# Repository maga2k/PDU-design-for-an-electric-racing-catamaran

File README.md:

# PDU-design-for-an-electric-racing-catamaran
Hardware and firmware implementation of a Power Distribution Unit (PDU) for an electric racing catamaran

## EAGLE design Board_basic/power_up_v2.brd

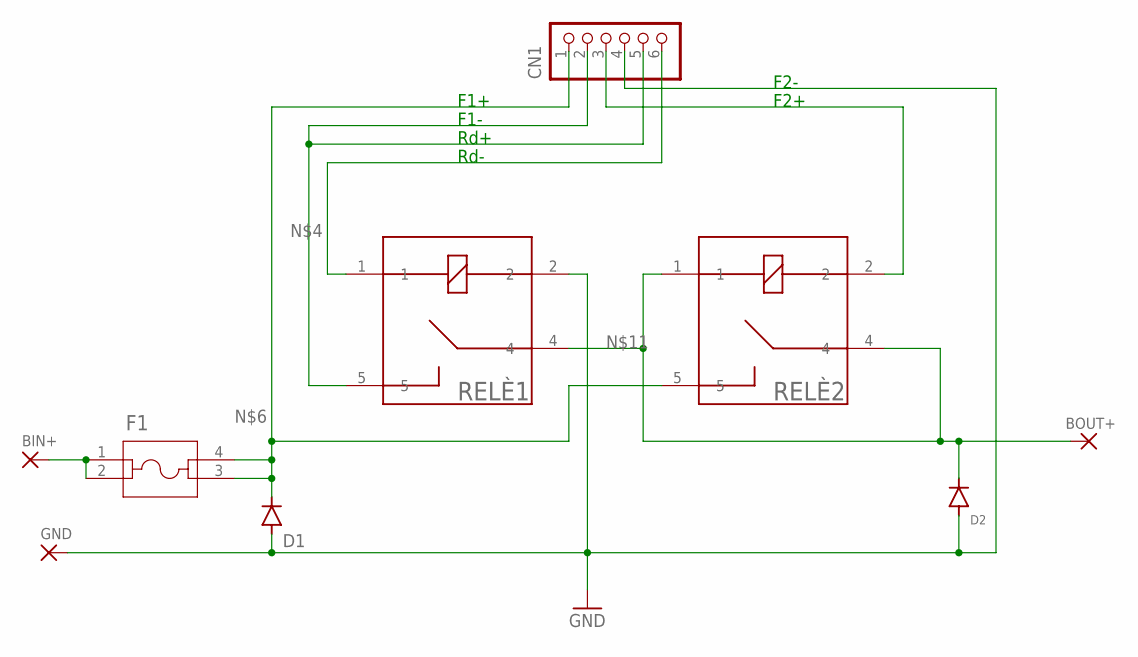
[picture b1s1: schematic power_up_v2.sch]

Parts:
BIN+: WIREPAD3,81/1,4; 12/0,7
BOUT+: WIREPAD3,81/1,4; 12/0,7
CN1: B6P-VH
D1, D2: BY550; DO27-15
F1: 3568; 3568_KEY
GND: WIREPAD3,81/1,4; 12/0,7
RELÈ1, RELÈ2: 1393280-5; RELAY_1393280-5

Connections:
GND: CN1.4, D1.A, D2.A, GND.1, RELÈ1.2
unnamed: BIN+.1, F1.1, F1.2
unnamed: CN1.2, CN1.5, RELÈ1.5
unnamed: CN1.3, RELÈ2.2
unnamed: CN1.1, D1.C, F1.3, F1.4, RELÈ2.5
unnamed: CN1.6, RELÈ1.1
unnamed: BOUT+.1, D2.C, RELÈ1.4, RELÈ2.1, RELÈ2.4

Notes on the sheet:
F1+
F1-
F2+
F2-
Rd+
Rd-

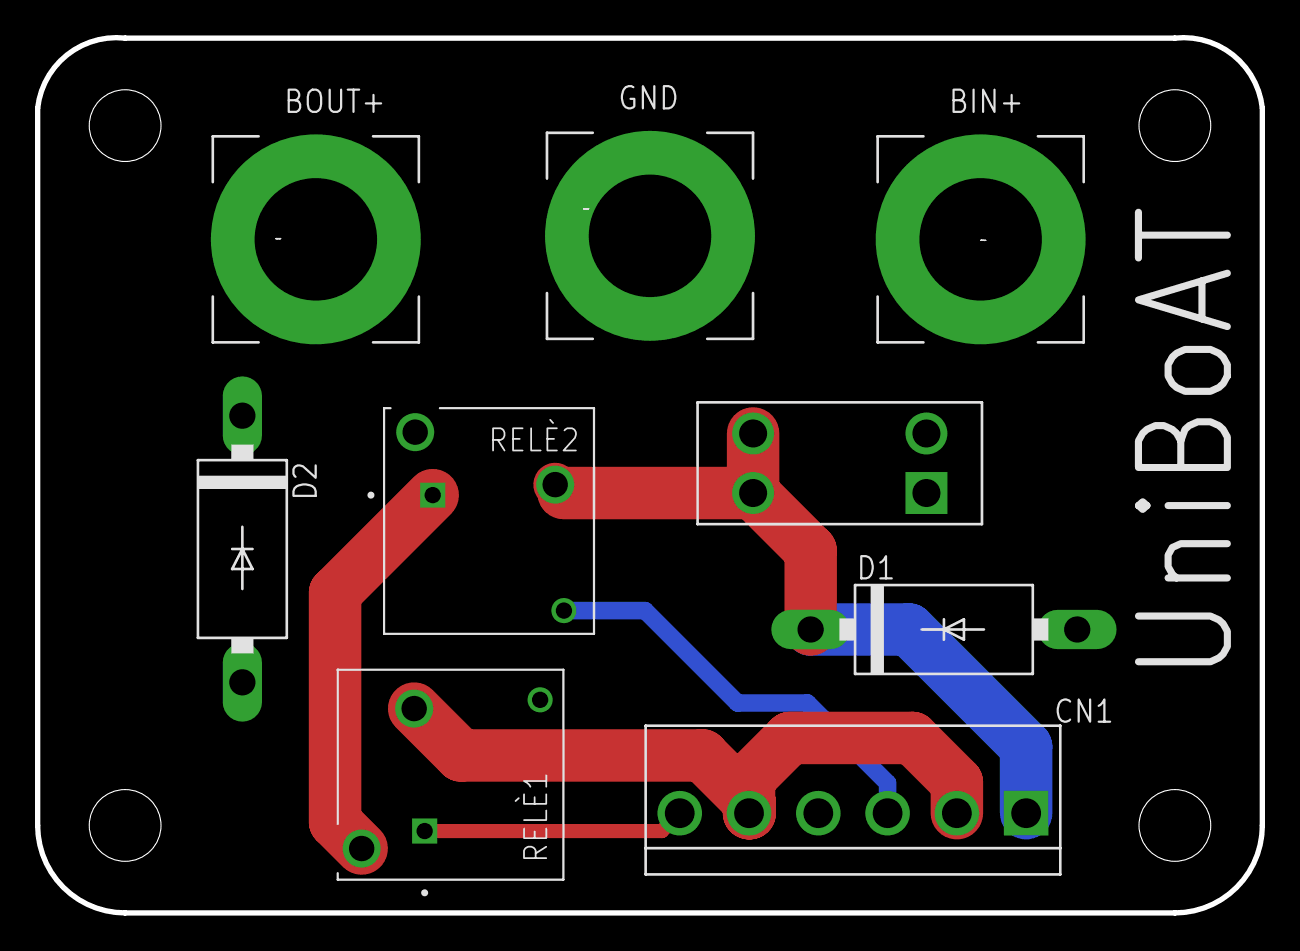
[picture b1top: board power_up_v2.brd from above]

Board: 2 copper layers, 70.0 x 50.0 mm, 13 parts (0 on the bottom side), 7 nets.

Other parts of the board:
U$1, U$2, U$3, U$4: M4_HOLE

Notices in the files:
parts and their libraries:
COPYRIGHT: Copyright (C) 2024 Ultra Librarian. All rights reserved.
